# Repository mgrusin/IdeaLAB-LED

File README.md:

<h1>InventHQ-LED
 
<h2>A simple PCB to help teach soldering skills

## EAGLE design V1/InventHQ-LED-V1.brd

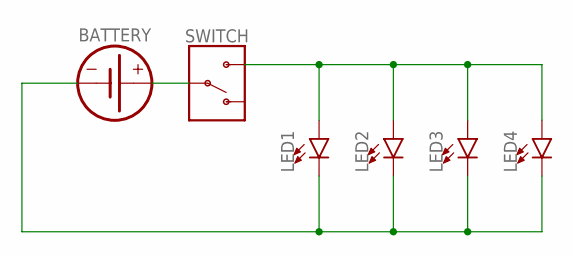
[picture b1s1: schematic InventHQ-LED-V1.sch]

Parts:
BATTERY: COIN_CELL_HOLDER_BH-25C-1; BH-25C-1
LED1, LED2, LED3, LED4: LED_5MM_MIKE
SWITCH: SWITCH-SPDT-PTH-11.6X4.0MM-KIT; SWITCH_SPDT_PTH_11.6X4.0MM_KIT

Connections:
unnamed: BATTERY.POS (+), SWITCH.2
unnamed: LED1.A, LED2.A, LED3.A, LED4.A, SWITCH.3 (S)
unnamed: BATTERY.NEG (-), LED1.K (C), LED2.K (C), LED3.K (C), LED4.K (C)

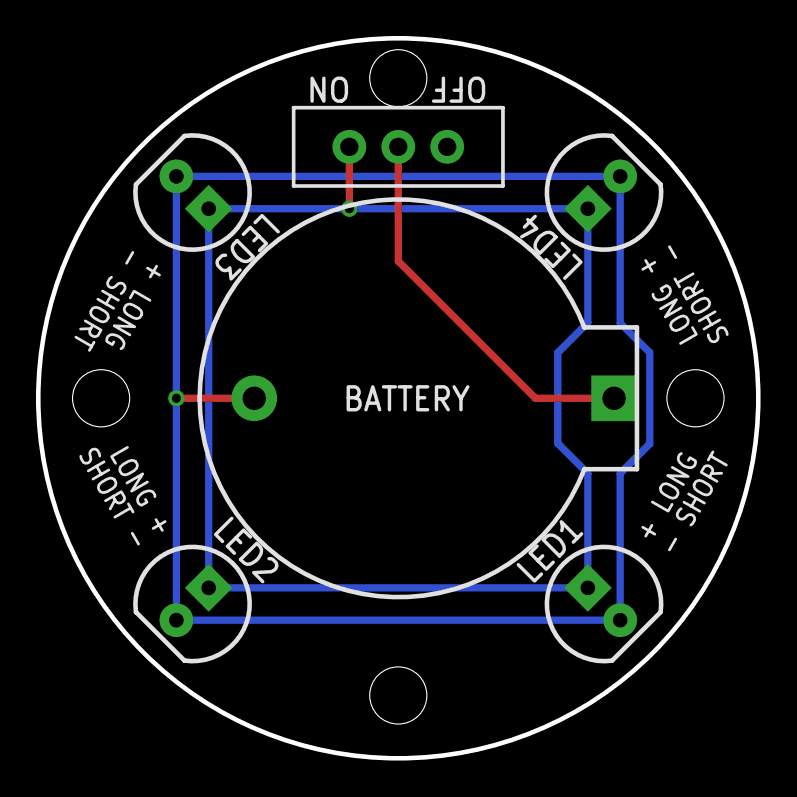
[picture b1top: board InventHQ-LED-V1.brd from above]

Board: 2 copper layers, 40.0 x 40.0 mm, 6 parts (0 on the bottom side), 3 nets.

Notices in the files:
parts and their libraries:
SparkFun-Switches: Licensing: Creative Commons ShareAlike 4.0 International - https://creativecommons.org/licenses/by-sa/4.0
